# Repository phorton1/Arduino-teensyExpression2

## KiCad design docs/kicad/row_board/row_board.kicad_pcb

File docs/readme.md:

# teensyExpression2 - a Consumer End User Product

I am making this project public at this time because it is an important
step in the devlopment of the
[**vGuitar rig**](https://github.com/phorton1/phorton1/).
The documentation here is a mess!

The sotftware herein has been tested, and is working on the original
[**teensyExpression**](https://github.com/phorton1/Arduino-teensyExpression)
hardware using a new motherboard PCB that is
included in that repository.

This repository is a major revision to the *teensyExpression*, a complete
rework, that provides most of the previous functionality, and a completely
different way of **configuring the pedal**, via **preference (rig) files**
that can be transferred to and from the device via a serial interface
and the
[Buddy](https://github.com/phorton1/base-apps-buddy) and
[fileClient](https://github.com/phorton1/base-apps-fileClient) applications,
or copied to the SDCard on the teensy in an any other manner.
This new way of configuring the pedal is intended to make it
completely generalized, and usable for any purpose, without the
need to re-compile or re-install the firmware, and yet, to be, by
default, completely configured for use within the gVuitar rig.

During this re-development effort, all new Fusion 360 3D designs for the
Pedal were produced, though never printed.  During that process a serious
review of the electronics involved in the entire vGuitar rig led to a
re-thinking of its entire architecture, and the role of the teensyExpression
pedal within that architecture, leading to the notion of a new, as yet
un-created, **teensyEpression3 repository** that will contain the streamlined
and well documented source code, 3D files, kicad circuits, and so on.

I am in the *proof of concept* stage with this next step in the
vGuitar rig journey.  For anyone following along, that next step
is the new
teensyPiAudio
repository that I am initializing today as
a public repository, which will contain the work that I am doing
on a day to day basis these days.

Please feel free to peruse this repository and/or see the new
work I am doing at

**Patrick** - May 6, 2024

**p.s. - in order to do this I am pushing a large amount of uncoordinated
and unstreamlined stuff to github, particularly a bunch of new components
and footprints for **kicad**. All that will need to be cleaned up too.

## OLD

Use the looper rig as an archetype of the types of rigs that can be programmed.

Most of the other functionality of the system will be maintained, including things like

- host port?
- ftp tuning and sensitvity
- midi monitoring at excruciating levels of detail
- serial port
- debugging output to serial port or USB
- midi monitoring to serial port or USB
- midi sequences sent to serial port or USB

Before going into excruciating detail, I want to see if I can specify a
language that will let me recreate my exist looper rig.

##  Rig Basics

There will be text files on the SD card that can contain *user defined rigs*.

An *example.rig* will be provided which just happens to generate the default
**iPadLooper** rig. I will have a way to that convert that to an H file containing
the necessary parsed representation for the default constant rig.

In my const version, the default rig will have the name of **iPadLooper** and will be
used on a *factory reset*. The *default rig name* of iPadLooper will be *reserved* for
use by the system.

All **rig names** shall be limited to the characters a-z, A-z, 0-9,
space, dash, and underscore.

## Load

*Load* shall present a list of legal rig names found on the SD card
(skipping the default rig name if happens to exist on disk),
with the default rig name at the top.

A rig loaded from disk will be checked for syntactical and
functional correctness.  A failure to Load the rig will not
change anything in the system (the current rig will remain
active).

Loading a rig will place it in memory and activate it.

It is not clear at this time if the current_rig name is
stored immediately in preferences, or if it will sommehow
be tied to the preferences system.

I suspect it will be stored immediately upon a load,
and not have anything to do with the Preferences.

## Boot

Upon booting the default rig will be set into memory.
If the current_rig preference is not the same as the
default rig name, an attempt will be made to load the
given rig from the SD card.

If the named rig is succesfully loaded, it will be placed
in memory and activated.   Otherwise, default rig will
be used.

The preference will not be changed as a result of a
failure to read a file that was previously successfully
saved, although an error message WILL be generated.

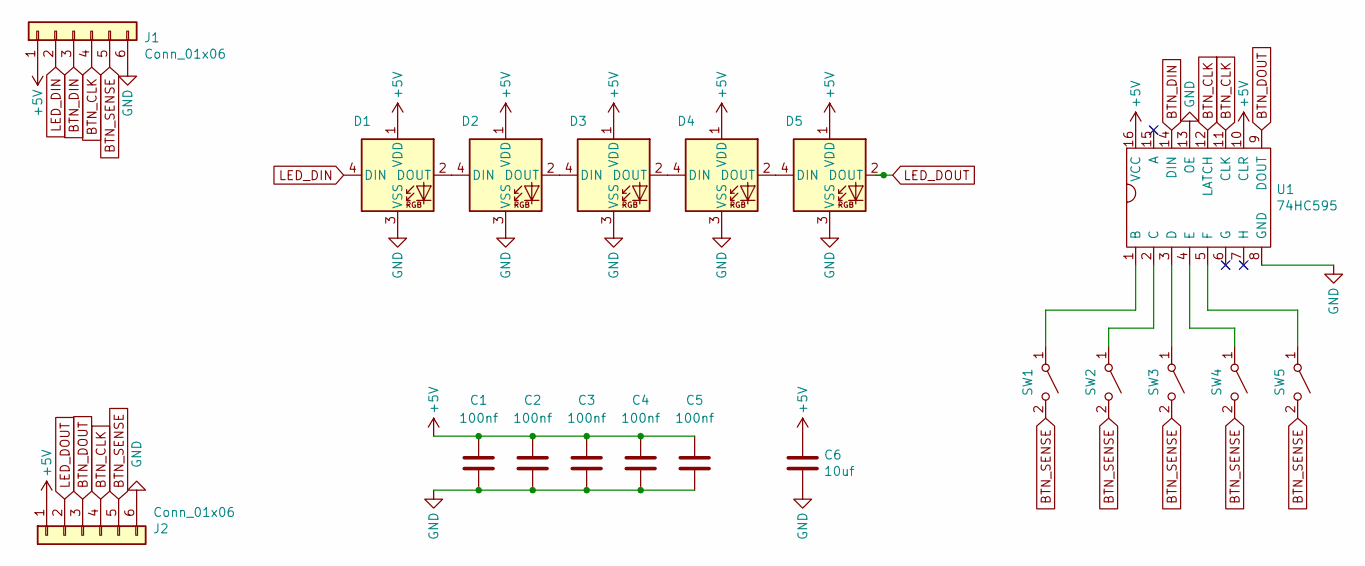
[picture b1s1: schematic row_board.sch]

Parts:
C1, C2, C3, C4, C5: 100nf; C_1206_3216Metric_Pad1.42x1.75mm_HandSolder
C6: 10uf; C_1206_3216Metric_Pad1.42x1.75mm_HandSolder
D1, D2, D3, D4, D5: WS2812B; myWS2812
J1, J2: Conn_01x06; my6Pin-08mm
SW1, SW2, SW3, SW4, SW5: SW1; mySwitchSoft
U1: 74HC595; TSSOP-16_4.4x5mm_P0.65mm

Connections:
+5V: C1.1, C2.1, C3.1, C4.1, C5.1, C6.1, D1.1 (VDD), D2.1 (VDD), D3.1 (VDD), D4.1 (VDD), D5.1 (VDD), J1.1, J2.1, U1.10 (CLR), U1.16 (VCC)
CLK: J1.4, J2.4, U1.11 (CLK), U1.12 (LATCH)
DIN: D1.4 (DIN), J1.2
DOUT: D5.2 (DOUT), J2.2
GND: C1.2, C2.2, C3.2, C4.2, C5.2, C6.2, D1.3 (VSS), D2.3 (VSS), D3.3 (VSS), D4.3 (VSS), D5.3 (VSS), J1.6, J2.6, U1.8 (GND), U1.13 (OE)
unnamed: D1.2 (DOUT), D2.4 (DIN)
unnamed: D2.2 (DOUT), D3.4 (DIN)
unnamed: D3.2 (DOUT), D4.4 (DIN)
unnamed: D4.2 (DOUT), D5.4 (DIN)
unnamed: SW1.1 (A), U1.1 (B)
unnamed: SW2.1 (A), U1.2 (C)
unnamed: SW3.1 (A), U1.3 (D)
unnamed: SW4.1 (A), U1.4 (E)
unnamed: SW5.1 (A), U1.5 (F)
SW: J1.5, J2.5, SW1.2 (B), SW2.2 (B), SW3.2 (B), SW4.2 (B), SW5.2 (B)
SWIN: J1.3, U1.14 (DIN)
SWOUT: J2.3, U1.9 (DOUT)

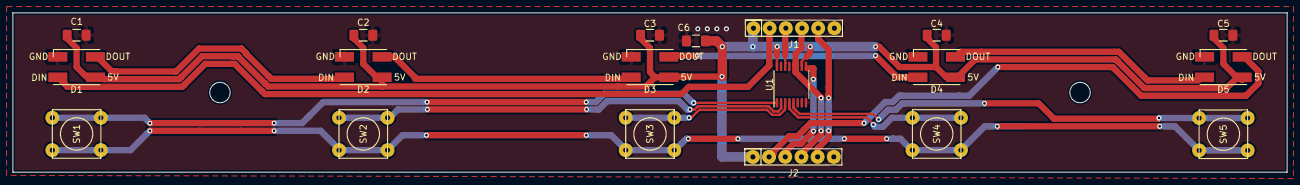
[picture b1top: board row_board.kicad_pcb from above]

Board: 2 copper layers, 200.0 x 25.0 mm, 19 parts (0 on the bottom side), 17 nets.

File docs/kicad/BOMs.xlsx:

|  |  |  | bqty | boards
 | row board | U | 74HC595 | 1 | 9
 | row board | L | WS2812b | 5 | 9
 | row board | C | 100nf | 5 | 9
 | row board | CP | 10uf | 1 | 9
 | octo interface | CP | 10uf | 6 | 3
 | octo interface | C | 2.7nf | 2 | 3
 | octo interface | C | 1.5nf | 2 | 3
 | octo interface | R | 10K | 10 | 3
 | octo interface | R | 100K | 2 | 3
 | octo interface | R | 562 | 2 | 3
 | octo interface | R | 150 | 2 | 3

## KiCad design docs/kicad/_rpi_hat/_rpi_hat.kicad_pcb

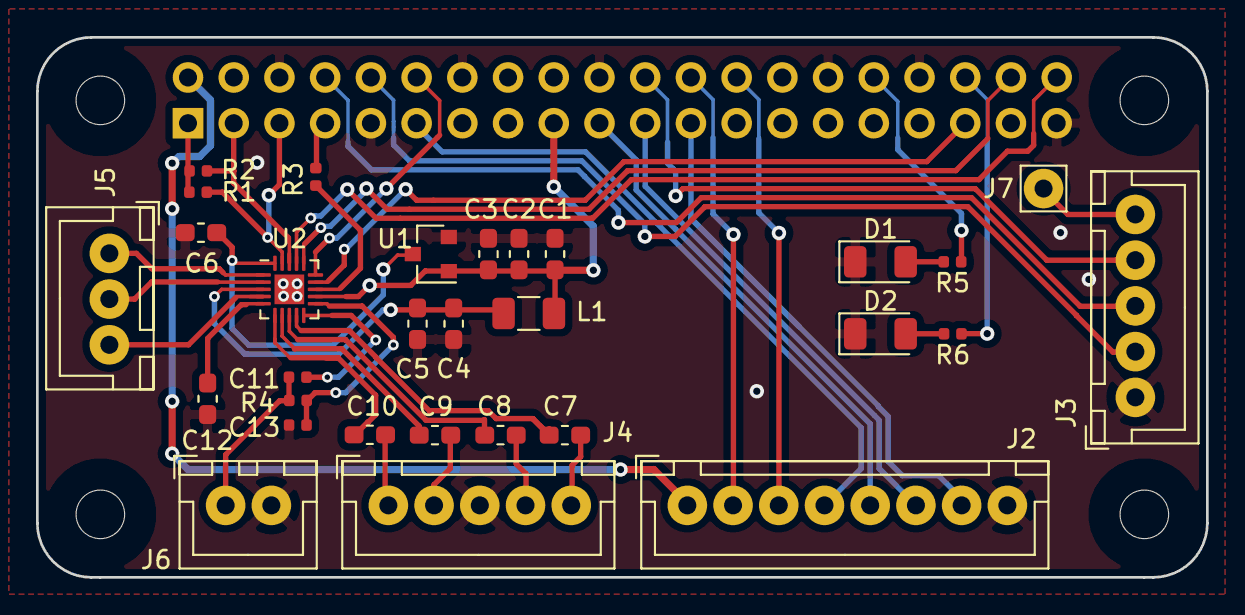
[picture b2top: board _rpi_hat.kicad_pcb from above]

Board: 2 copper layers, 65.0 x 30.0 mm, 35 parts (1 on the bottom side), 42 nets.

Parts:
C1, C4, C6, C7, C8, C9, C10: 2.2uf; C_0603_1608Metric_Pad1.05x0.95mm_HandSolder
C2, C3, C5: 0.1uf; C_0603_1608Metric_Pad1.05x0.95mm_HandSolder
C11: 0.1uf; C_0402_1005Metric
C12: 0.15uf; C_0603_1608Metric_Pad1.05x0.95mm_HandSolder
C13: 2.2uf; C_0402_1005Metric
D1, D2: LED; LED_1206_3216Metric
H1, H2, H3, H4: MountingHole; MountingHole_2.7mm_M2.5_uHAT_RPi
J1: GPIO_CONNECTOR; PinSocket_2x20_P2.54mm_Vertical_Centered_Anchor
J2: display; myJSTx08
J3: esp32; myJSTx05
J4: audio; myJSTx05
J5: HP; myJSTx03
J6: mic; myJSTx02
J7: RPI_RUN; myPinHeader_1x01
L1: Ferrite 600; L_1206_3216Metric
R1, R2, R4, R5, R6: 2.2k; R_0402_1005Metric
R3: 100; R_0402_1005Metric
U1: AP7313-18; SOT-23
U2: pauls_sgtl_5000_20; QFN-20-1EP_3x3mm_P0.4mm_EP1.65x1.65mm

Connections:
+3V3: C1.1, C2.1, C3.1, J1.1, J1.17, L1.1, R1.1, R2.1, U1.1, U2.12
+5V: J1.2, J1.4, J2.1
GND: C1.2, C2.2, C3.2, C4.2, C5.2, C6.2, C12.2, C13.2, D1.1, D2.1, J1.6, J1.9, J1.14, J1.20, J1.25, J1.30, J1.34, J1.39, J2.8, J3.1, J4.3, J6.2, U1.2, U2.21
HP_GND: J5.2, U2.2
HP_L: J5.3, U2.4
HP_R: J5.1, U2.1
I2S_RX_ACTIVE: J1.32, R5.1
I2S_TX_ACTIVE: J1.36, R6.1
LED_CS: J1.24, J2.2
LINEIN_L: C7.2, J4.5
LINEIN_R: C8.2, J4.4
LINEOUT_L: C9.2, J4.2
LINEOUT_R: C10.2, J4.1
MIC_IN: C11.2, J6.1, R4.2
MISO: J1.21, J2.6
MOSI: J1.19, J2.5
unnamed: C4.1, C5.1, L1.2, U2.3
unnamed: C6.1, U1.3, U2.20
unnamed: C7.1, U2.9
unnamed: C8.1, U2.8
unnamed: C9.1, U2.7
unnamed: C10.1, U2.6
unnamed: C11.1, U2.10
unnamed: C12.1, U2.5
unnamed: C13.1, R4.1, U2.11
unnamed: D1.2, R5.2
unnamed: D2.2, R6.2
unnamed: R3.2, U2.13
RPI_READY: J1.22, J3.4
RPI_RUN: J3.5, J7.1
RPI_RX: J1.10, J3.2
RPI_TX: J1.8, J3.3
SCL: J1.5, R1.2, U2.19
SCLK: J1.23, J2.7
SDA: J1.3, R2.2, U2.18
SGTL_BLCK: J1.12, U2.15
SGTL_FCLK: J1.35, U2.14
SGTL_I2S_IN: J1.40, U2.17
SGTL_I2S_OUT: J1.38, U2.16
SGTL_MCLK: J1.7, R3.1
TFT_CD: J1.11, J2.4
TOUCH_CS: J1.26, J2.3

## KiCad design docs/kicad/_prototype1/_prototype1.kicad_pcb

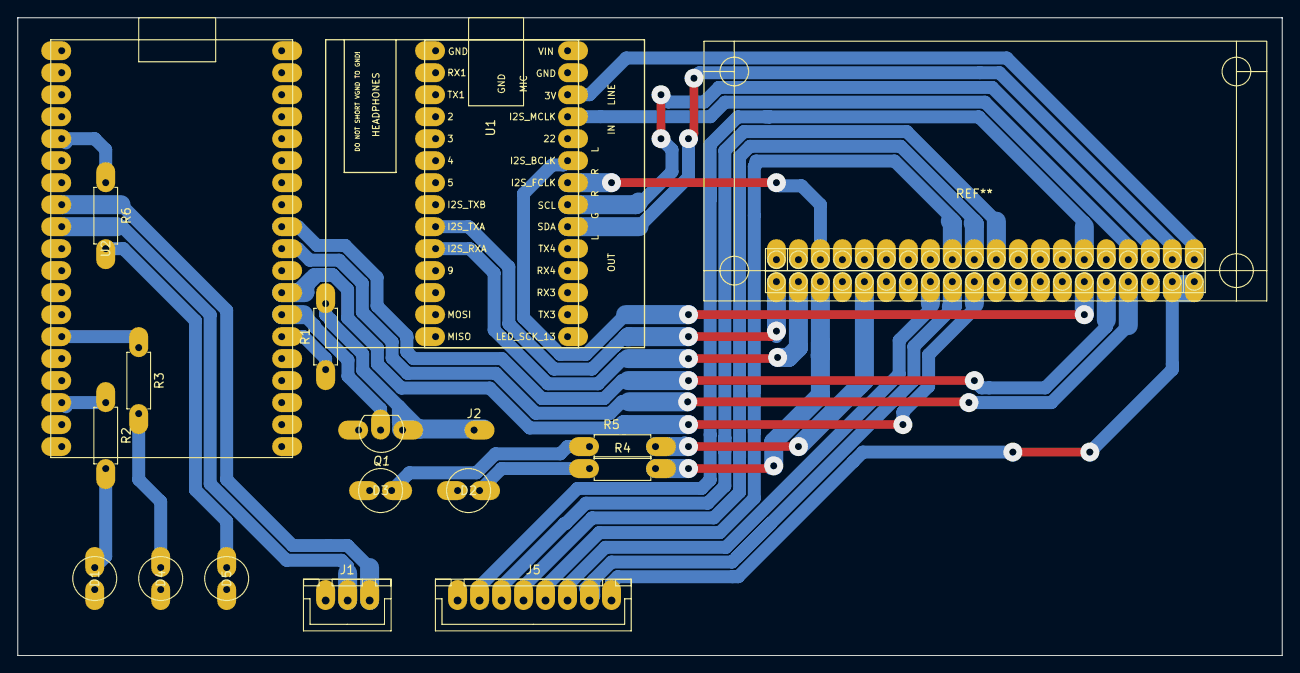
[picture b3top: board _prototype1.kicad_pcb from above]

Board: 2 copper layers, 146.1 x 73.7 mm, 19 parts (0 on the bottom side), 34 nets.

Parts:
D1: RED; led_red
D2, D3: yellow; led_yellow
D4: GREEN; led_green
D5: BLUE; led_blue
J1: T4 Serial; JST3
J2: RPI_RUN; Oval1Pin
J3: rpiB; pinSocket1x20
J4: rpiA; pinSocket1x20
J5: RPI_ILI9488; JST8
Q1: BC547; transistor
R1, R2, R3, R4, R5: 220; resistor
R6: 560; resistor
U1: teensyAudioRevD; audioShieldRevD
U2: ESP32_DEV; esp32_dev

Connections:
GND: D1.1, D2.1, D3.1, D4.1, D5.1, J1.1, J3.1, J3.8, J3.16, J4.3, J4.7, J4.10, J4.15, J4.17, J5.1, Q1.3, U1.27, U2.6, U2.20, U2.26
I2S_BCLK: J4.6, U1.23
I2S_FCLK: J3.3, U1.22
I2S_MCLK: J3.17, U1.25
I2S_RX: J4.19, U1.10
I2S_TX: J4.20, U1.9
LED_ALIVE: R2.1, U2.22
LED_PI_READY: R6.1, U2.34
LED_PI_RUN: R3.1, U2.25
unnamed: D1.2, R2.2
unnamed: D2.2, R4.1
unnamed: D3.2, R5.1
unnamed: D4.2, R3.2
unnamed: D5.2, R6.2
PI_REBOOT: Q1.2, U2.13
RPI_3V: J3.20, U1.26
RPI_5V: J4.1, J4.2, J5.8
RPI_CD: J3.15, J5.2
RPI_I2S_RX_ACTIVE: J4.16, R5.2
RPI_I2S_TX_ACTIVE: J4.18, R4.2
RPI_LED_CS: J4.12, J5.7
RPI_MISO: J3.10, J5.4
RPI_MOSI: J3.11, J5.3
RPI_READY: J4.11, U2.12
RPI_RUN: J2.1, Q1.1, R1.2
RPI_RX: J4.5, U2.9
RPI_SCL: J3.18, U1.21
RPI_SCLK: J3.9, J5.5
RPI_SDA: J3.19, U1.20
RPI_TOUCH_CS: J4.13, J5.6
RPI_TX: J4.4, U2.10
SENS_PI_RUN: R1.1, U2.14
T4_RX1: J1.2, U2.30
T4_TX1: J1.3, U2.31

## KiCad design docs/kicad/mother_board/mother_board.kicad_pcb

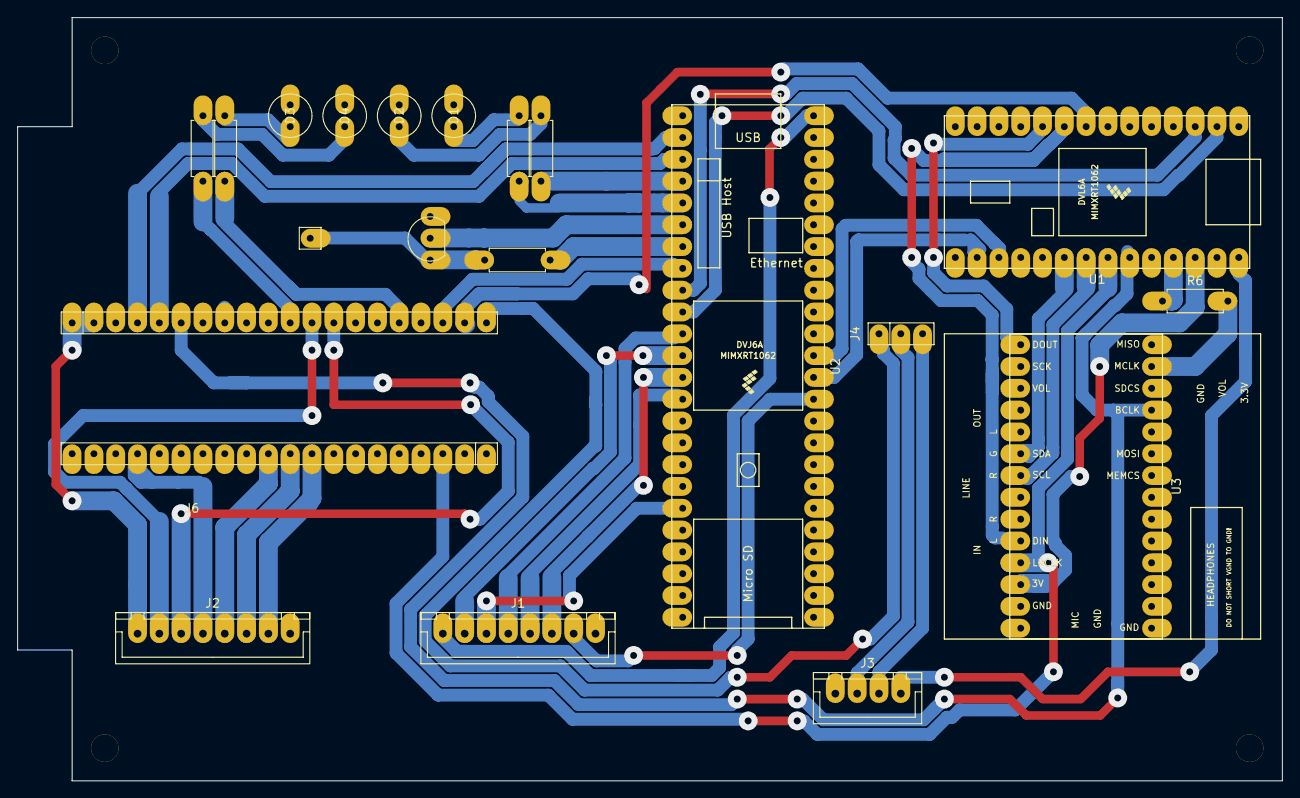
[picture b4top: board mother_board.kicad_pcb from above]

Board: 2 copper layers, 147.3 x 88.9 mm, 21 parts (0 on the bottom side), 47 nets.

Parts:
D1: GREEN; led_green
D2: BLUE; led_blue
D3, D4: YELLOW; led_yellow
J1: T3_ILI9488; JST8
J2: RPI_ILI9488; JST8
J3: USB Host; JST4
J4: 40 bottom; pinSocket1x3
J5: RPI_RUN; pinSocket1x1
J6: rpiB; pinSocket1x20
J7: rpiA; pinSocket1x20
Q1: BC547; transistor
R1, R3, R4, R5: 220; resistor
R2: 560; resistor
R6: 100; resistor
U1: myTeensy4.0; teensy40
U2: myTeensy4.1; teensy41
U3: teensyAudioRevB; audioShieldRevB

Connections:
GND: D1.1, D2.1, D3.1, D4.1, J1.8, J2.8, J3.1, J6.1, J6.8, J6.16, J7.3, J7.7, J7.10, J7.15, J7.17, Q1.3, U1.1, U1.27, U2.1, U2.34, U2.47, U3.1, U3.27
HOST_D+: J3.2, J4.2
HOST_D-: J3.3, J4.3
I2S_BCLK: J7.6, U1.23, U3.11
I2S_FCLK: J6.3, U1.22, U3.25
I2S_MCLK: R6.1, U1.25
I2S_RXA: U1.10, U3.15
I2S_RXB: J4.1, J7.20
I2S_TXA: U1.9, U3.24
I2S_TXB: J7.19, U1.8
LED_PI_READY: R2.1, U2.4
LED_PI_RUN: R1.1, U2.5
unnamed: D1.2, R1.2
unnamed: D2.2, R2.2
unnamed: D3.2, R3.2
unnamed: D4.2, R4.2
unnamed: R6.2, U3.13
PI_REBOOT: Q1.2, U2.6
RPI_5V: J2.1, J7.1, J7.2
RPI_CD: J2.4, J6.17
RPI_I2S_RX_ACTIVE: J7.11, R4.1
RPI_I2S_TX_ACTIVE: J7.16, R3.1
RPI_LED_CS: J2.2, J7.12
RPI_MISO: J2.6, J6.10
RPI_MOSI: J2.5, J6.11
RPI_READY: J7.18, U2.8
RPI_RUN: J5.1, Q1.1, R5.2
RPI_RX: J7.5, U2.3
RPI_SCLK: J2.7, J6.9
RPI_TOUCH_CS: J2.3, J7.13
RPI_TX: J7.4, U2.2
SENS_PI_RUN: R5.1, U2.7
T40_3.3V: U1.26, U3.26
T40_5V: J3.4, U1.28
T40_RX1: U1.2, U2.10
T40_RX3: U1.17, U2.37
T40_SCA: U1.20, U3.20
T40_SCL: U1.21, U3.21
T40_TX1: U1.3, U2.9
T40_TX3: U1.16, U2.36
T41_5V: J1.1, U2.48
T41_CD: J1.4, U2.11
T41_LED_CS: J1.2, U2.12
T41_MISO: J1.5, U2.14
T41_MOSI: J1.6, U2.13
T41_SCLK: J1.7, U2.35
T41_TOUCH_CS: J1.3, U2.19

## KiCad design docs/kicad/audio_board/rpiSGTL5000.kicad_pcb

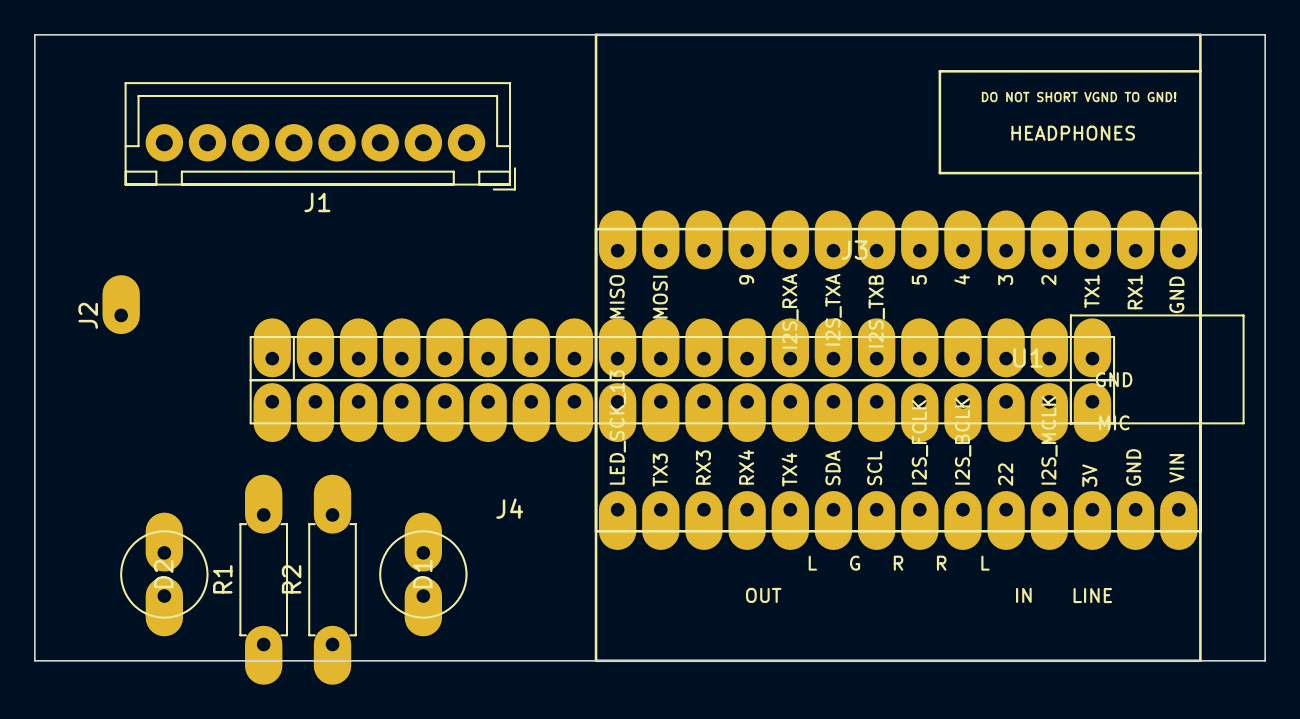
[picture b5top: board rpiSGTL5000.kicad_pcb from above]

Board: 2 copper layers, 72.4 x 36.8 mm, 9 parts (0 on the bottom side), 20 nets, no tracks yet.

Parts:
D1, D2: yellow; led_yellow
J1: display; myJSTx08
J2: RPI_RUN; Oval1Pin
J3: rpiB; pinSocket1x20_bottom
J4: rpiA; pinSocket1x20_bottom
R1, R2: 220; resistor
U1: teensyAudioRevD; audioShieldRevD

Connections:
+3V3: J3.20, U1.26
+5V: J1.8, J4.1, J4.2
GND: D1.1, D2.1, J1.1, J3.1, J3.8, J3.16, J4.3, J4.7, J4.10, J4.15, J4.17, U1.27
I2S_BCLK: J4.6, U1.23
I2S_FCLK: J3.3, U1.22
I2S_MCLK: J3.17, U1.25
I2S_RX: J4.19, U1.9
I2S_TX: J4.20, U1.10
unnamed: D1.2, R1.1
unnamed: D2.2, R2.1
RPI_CD: J1.5, J3.15
RPI_I2S_RX_ACTIVE: J4.11, R2.2
RPI_I2S_TX_ACTIVE: J4.16, R1.2
RPI_LED_CS: J1.7, J4.12
RPI_MISO: J1.3, J3.10
RPI_MOSI: J1.4, J3.11
RPI_SCLK: J1.2, J3.9
RPI_TOUCH_CS: J1.6, J4.13
SCL: J3.18, U1.21
SDA: J3.19, U1.20

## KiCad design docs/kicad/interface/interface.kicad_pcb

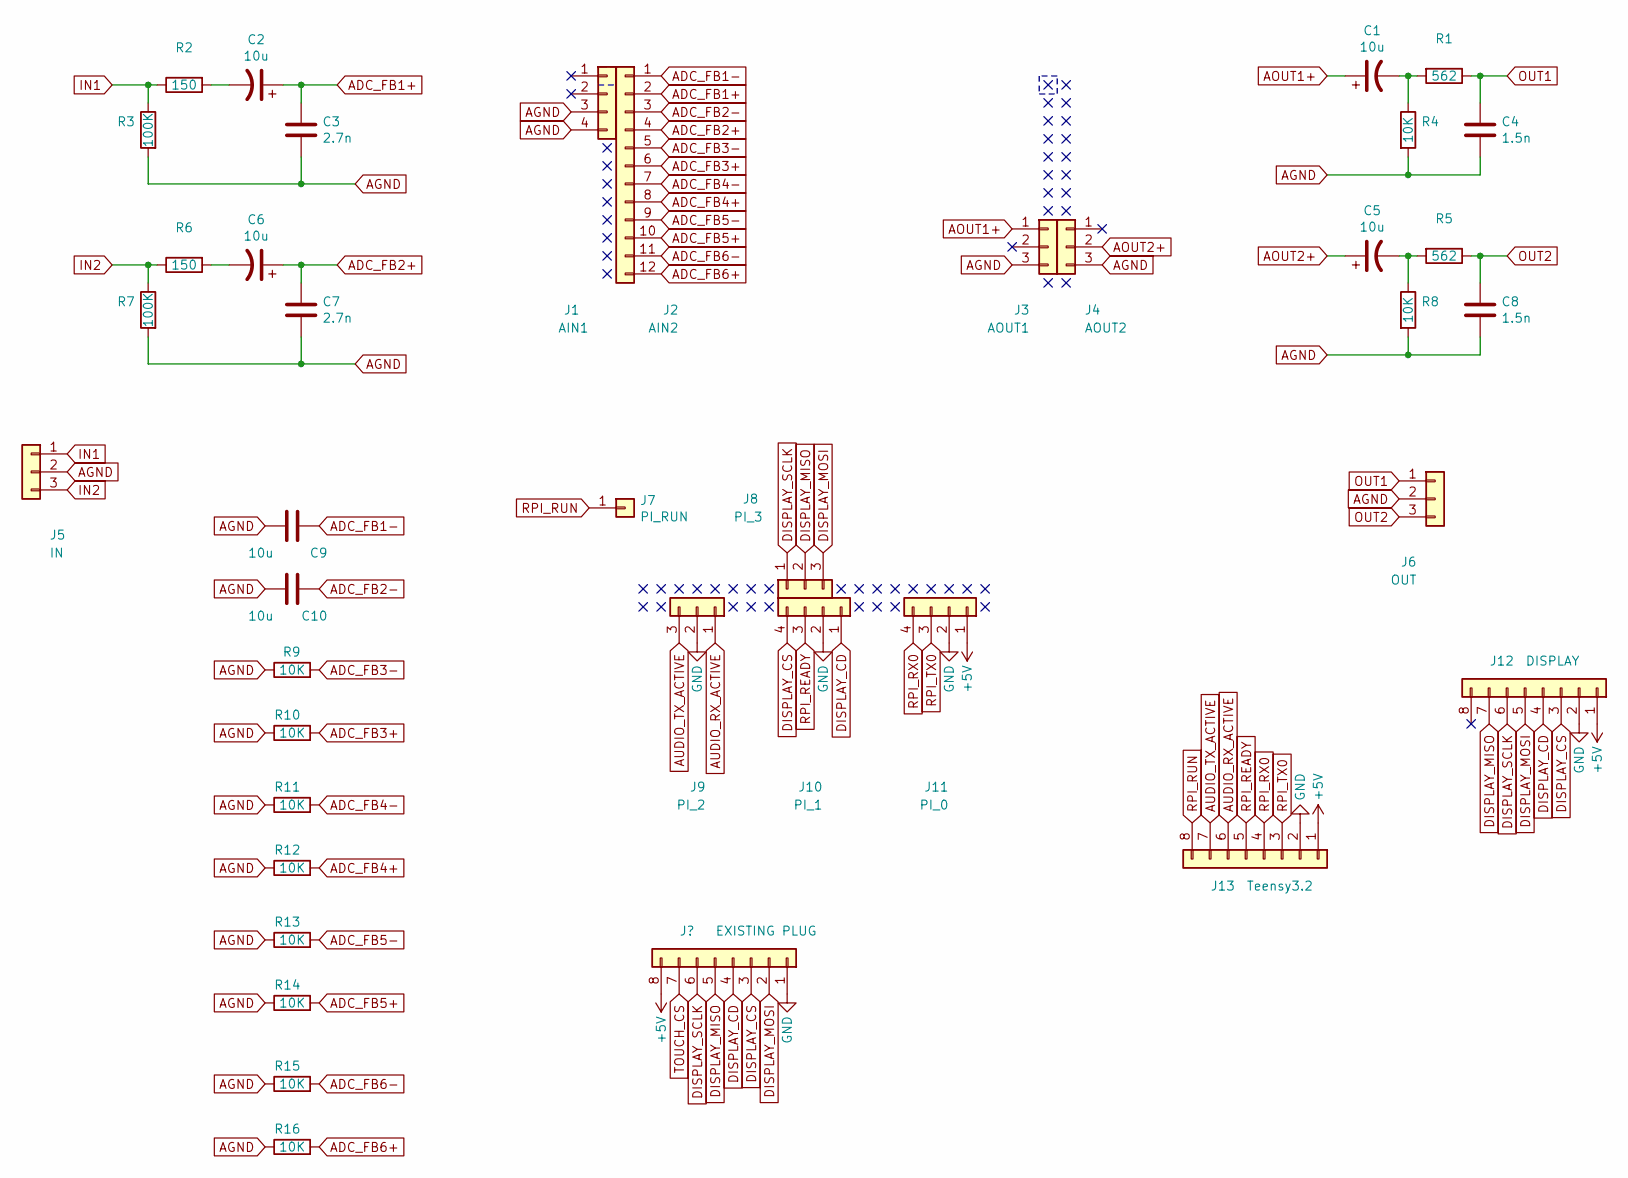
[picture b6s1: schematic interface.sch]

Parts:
C1, C2, C5, C6, C9, C10: 10u; CP_my10uf
C3, C7: 2.7n; my2pin
C4, C8: 1.5n; my2pin
J1: AIN1; my4pin
J2: AIN2; my14Pin
J3: AOUT1; my3pin
J4: AOUT2; my3pin
J5: IN; my3pin
J6: OUT; my3pin
J7: PI_RUN; my1pin
J8: PI_3; my3pin
J9: PI_2; my3pin
J10: PI_1; my4pin
J11: PI_0; my4pin
J12: DISPLAY; my8Pin
J13: Teensy3.2; my8Pin
R1, R5: 562; myResistor
R2, R6: 150; myResistor
R3, R7: 100K; myResistor
R4, R8, R9, R10, R11, R12, R13, R14, R15, R16: 10K; myResistor

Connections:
+5V: J11.1, J12.1, J13.1
ADC_FB1+: C2.1, C3.1, J2.2
ADC_FB1-: C9.1, J2.1
ADC_FB2+: C6.1, C7.1, J2.4
ADC_FB2-: C10.1, J2.3
ADC_FB3+: J2.6, R10.2
ADC_FB3-: J2.5, R9.2
ADC_FB4+: J2.8, R12.2
ADC_FB4-: J2.7, R11.2
ADC_FB5+: J2.10, R14.2
ADC_FB5-: J2.9, R13.2
ADC_FB6+: J2.12, R16.2
ADC_FB6-: J2.11, R15.2
AGND: C3.2, C4.2, C7.2, C8.2, C9.2, C10.2, J1.3, J1.4, J3.3, J4.3, J5.2, J6.2, R3.2, R4.2, R7.2, R8.2, R9.1, R10.1, R11.1, R12.1, R13.1, R14.1, R15.1, R16.1
AOUT1+: C1.1, J3.1
AOUT2+: C5.1, J4.2
AUDIO_RX_ACTIVE: J9.1, J13.6
AUDIO_TX_ACTIVE: J9.3, J13.7
DISPLAY_CD: J10.1, J12.4
DISPLAY_CS: J10.4, J12.3
DISPLAY_MISO: J8.2, J12.7
DISPLAY_MOSI: J8.3, J12.5
DISPLAY_SCLK: J8.1, J12.6
IN1: J5.1, R2.1, R3.1
IN2: J5.3, R6.1, R7.1
unnamed: C1.2, R1.2, R4.1
unnamed: C2.2, R2.2
unnamed: C5.2, R5.2, R8.1
unnamed: C6.2, R6.2
OUT1: C4.1, J6.1, R1.1
OUT2: C8.1, J6.3, R5.1
RPI_READY: J10.3, J13.5
RPI_RUN: J7.1, J13.8
RPI_RX0: J11.4, J13.4
RPI_TX0: J11.3, J13.3

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
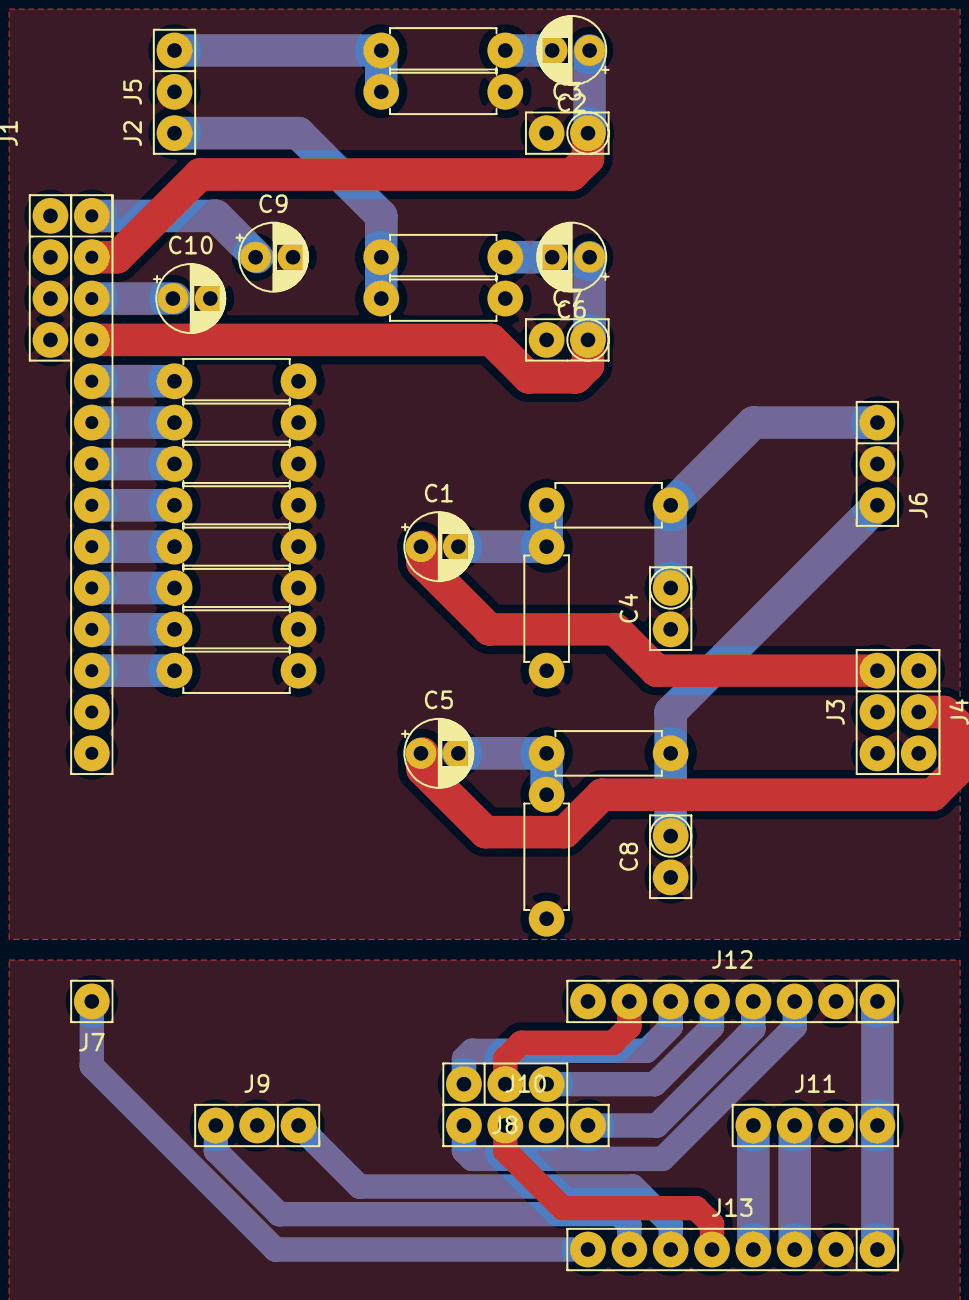
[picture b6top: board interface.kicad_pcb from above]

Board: 2 copper layers, 39 parts (0 on the bottom side), 36 nets.

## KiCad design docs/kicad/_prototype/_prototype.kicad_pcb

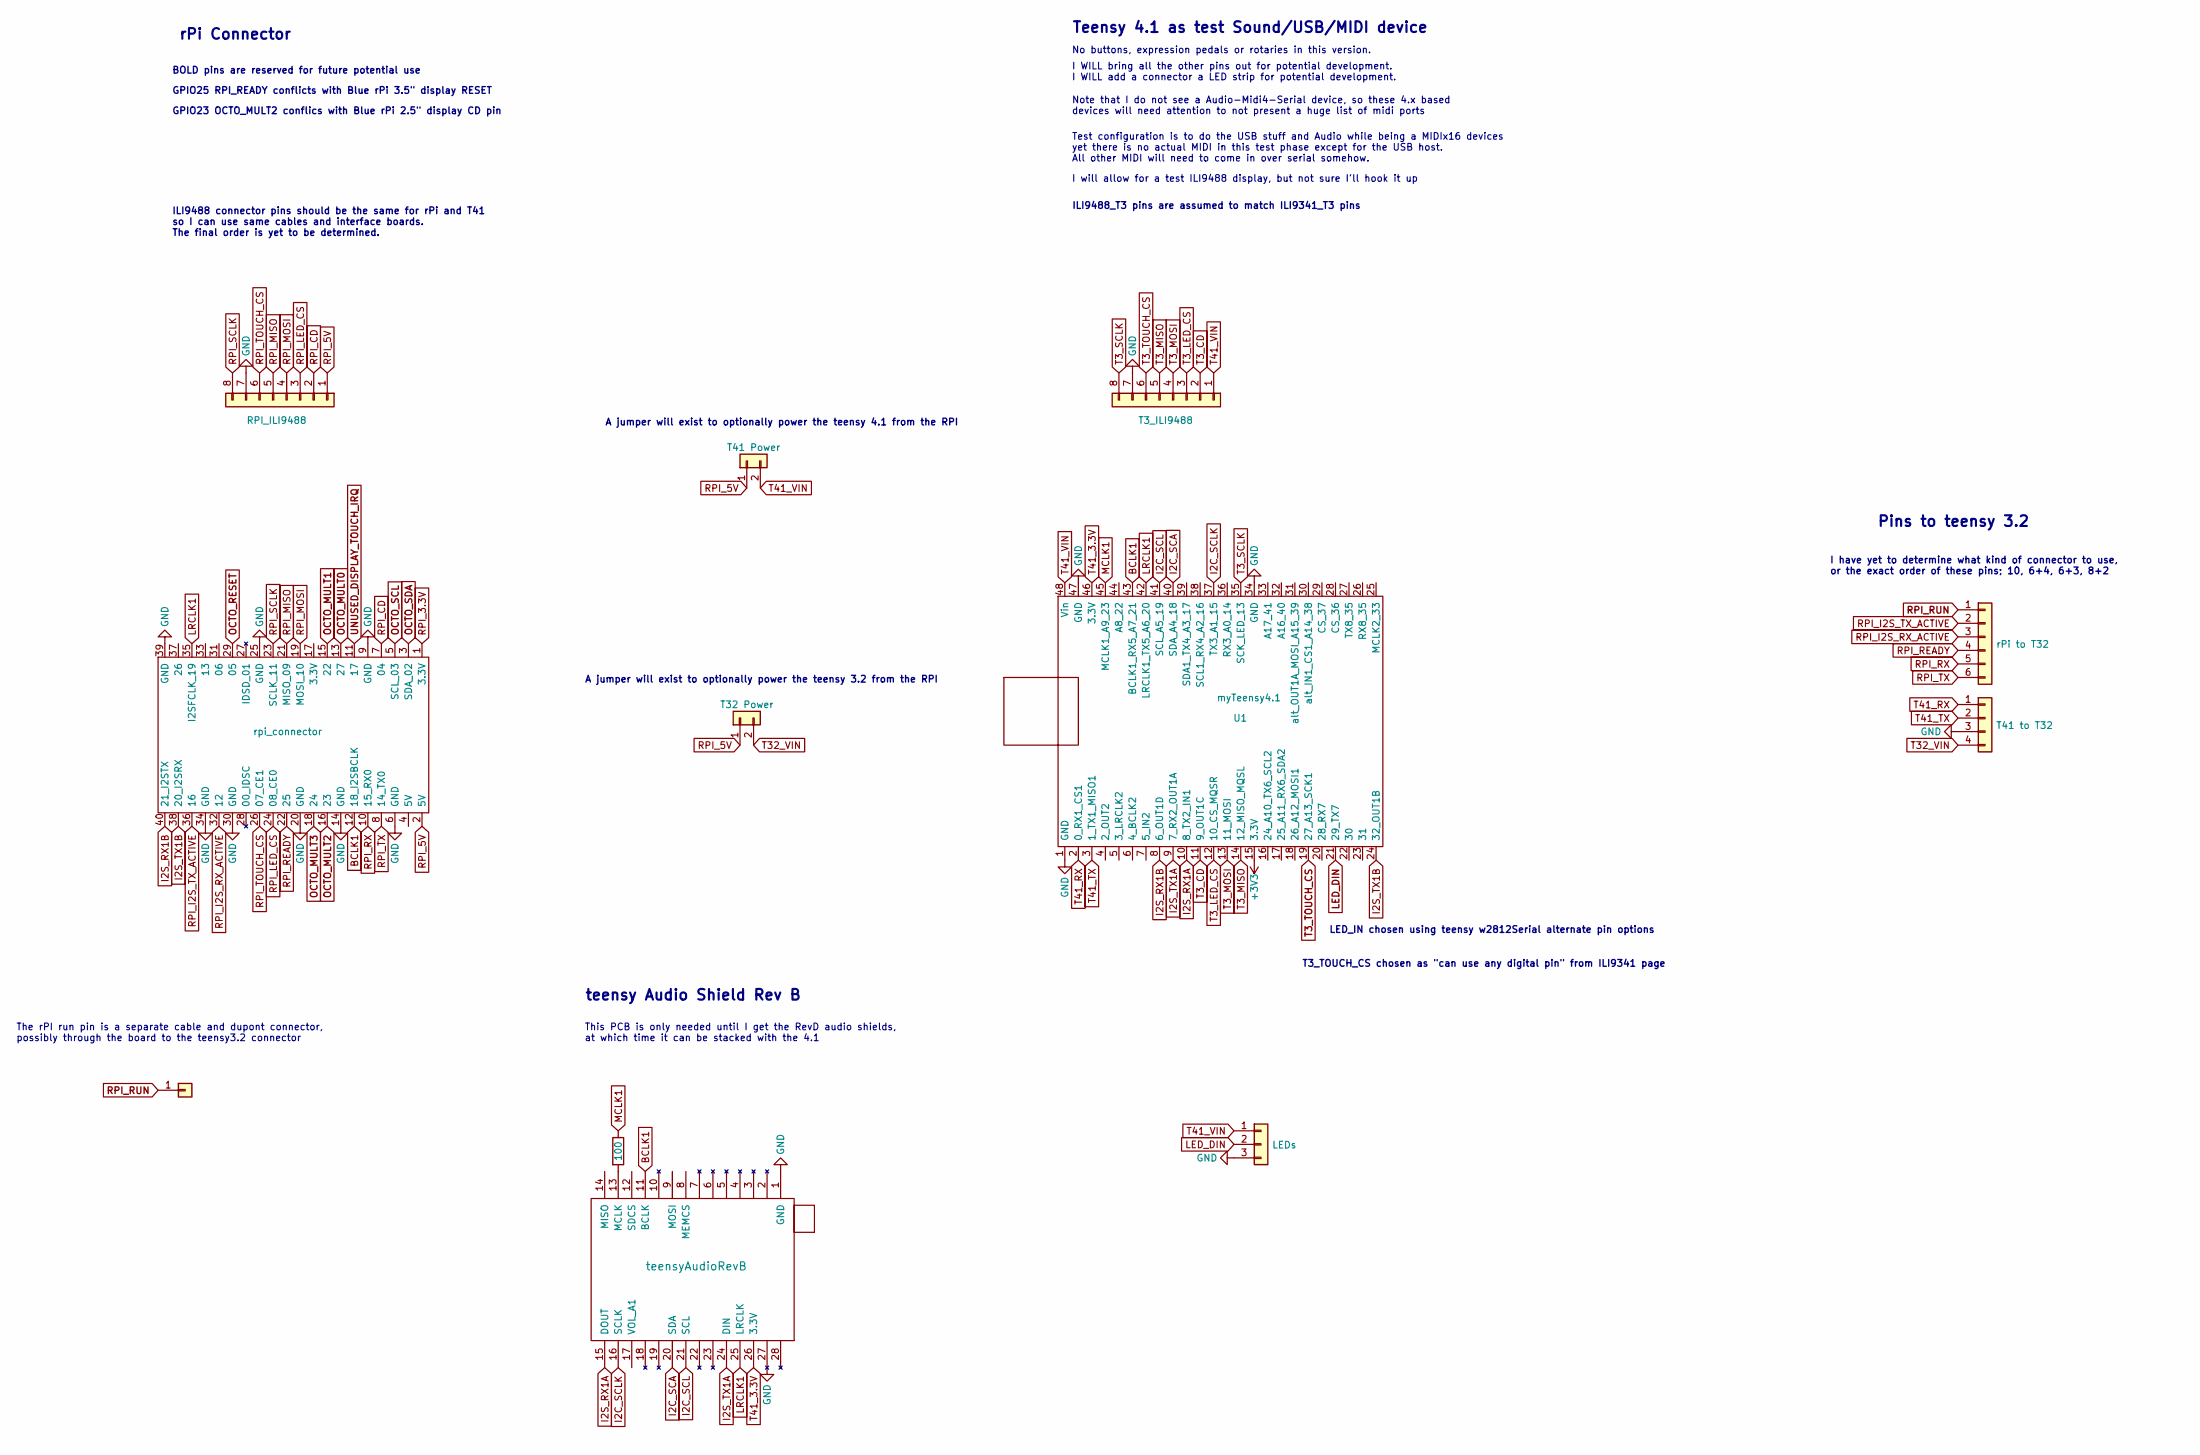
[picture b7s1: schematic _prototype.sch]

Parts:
J1: T3_ILI9488; myJSTx08
J2: RPI_ILI9488; myJSTx08
J3: T41 Power; myPinHeader_1x02
J5: rPi to T32; myJSTx06
J6: T32 Power; myPinHeader_1x02
J7: T41 to T32; myJSTx04
J8: rpi_connector; myRpiConnector
J9: RPI_RUN; my1pin
J10: LEDs; myJSTx03
R1: 100; myResistor
U1: myTeensy4.1; myTeensy41
U2: teensyAudioRevB; audioShieldRevB

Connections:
+3V3: U1.15 (3.3V)
BCLK1: J8.12 (18_I2SBCLK), U1.43 (BCLK1_RX5_A7_21), U2.11 (BCLK)
GND: J1.7, J2.7, J7.3, J8.6 (GND), J8.9 (GND), J8.14 (GND), J8.20 (GND), J8.25 (GND), J8.30 (GND), J8.34 (GND), J8.39 (GND), J10.3, U1.1 (GND), U1.34 (GND), U1.47 (GND), U2.1 (GND), U2.27
I2C_SCA: U1.40 (SDA_A4_18), U2.20 (SDA)
I2C_SCL: U1.41 (SCL_A5_19), U2.21 (SCL)
I2C_SCLK: U1.37 (TX3_A1_15), U2.16 (SCLK)
I2S_RX1A: U1.10 (8_TX2_IN1), U2.15 (DOUT)
I2S_RX1B: J8.40 (21_I2STX), U1.8 (6_OUT1D)
I2S_TX1A: U1.9 (7_RX2_OUT1A), U2.24 (DIN)
I2S_TX1B: J8.38 (20_I2SRX), U1.24 (32_OUT1B)
LED_DIN: J10.2, U1.21 (29_TX7)
LRCLK1: J8.35 (I2SFCLK_19), U1.42 (LRCLK1_TX5_A6_20), U2.25 (LRCLK)
MCLK1: R1.1, U1.45 (MCLK1_A9_23)
unnamed: R1.2, U2.13 (MCLK)
OCTO_MULT0: J8.13 (27)
OCTO_MULT1: J8.15 (22)
OCTO_MULT2: J8.16 (23)
OCTO_MULT3: J8.18 (24)
OCTO_RESET: J8.29 (05)
OCTO_SCL: J8.5 (SCL_03)
OCTO_SDA: J8.3 (SDA_02)
RPI_3.3V: J8.1 (3.3V)
RPI_5V: J2.1, J3.1, J6.1, J8.2 (5V)
RPI_CD: J2.2, J8.7 (04)
RPI_I2S_RX_ACTIVE: J5.3, J8.32 (12)
RPI_I2S_TX_ACTIVE: J5.2, J8.36 (16)
RPI_LED_CS: J2.3, J8.24 (08_CE0)
RPI_MISO: J2.5, J8.21 (MISO_09)
RPI_MOSI: J2.4, J8.19 (MOSI_10)
RPI_READY: J5.4, J8.22 (25)
RPI_RUN: J5.1, J9.1
RPI_RX: J5.5, J8.10 (15_RX0)
RPI_SCLK: J2.8, J8.23 (SCLK_11)
RPI_TOUCH_CS: J2.6, J8.26 (07_CE1)
RPI_TX: J5.6, J8.8 (14_TX0)
T3_CD: J1.2, U1.11 (9_OUT1C)
T3_LED_CS: J1.3, U1.12 (10_CS_MQSR)
T3_MISO: J1.5, U1.14 (12_MISO_MQSL)
T3_MOSI: J1.4, U1.13 (11_MOSI)
T3_SCLK: J1.8, U1.35 (SCK_LED_13)
T3_TOUCH_CS: J1.6, U1.19 (27_A13_SCK1)
T32_VIN: J6.2, J7.4
T41_3.3V: U1.46 (3.3V), U2.26 (3.3V)
T41_RX: J7.1, U1.2 (0_RX1_CS1)
T41_TX: J7.2, U1.3 (1_TX1_MISO1)
T41_VIN: J1.1, J3.2, J10.1, U1.48 (Vin)
UNUSED_DISPLAY_TOUCH_IRQ: J8.11 (17)

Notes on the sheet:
GPIO25 RPI_READY conflicts with Blue rPi 3.5" display RESET
GPIO23 OCTO_MULT2 conflics with Blue rPi 2.5" display CD pin
LED_IN chosen using teensy w2812Serial alternate pin options
T3_TOUCH_CS chosen as "can use any digital pin" from ILI9341 page
BOLD pins are reserved for future potential use
rPi Connector
teensy Audio Shield Rev B
This PCB is only needed until I get the RevD audio shields, at which time it can be stacked with the 4.1
ILI9488_T3 pins are assumed to match ILI9341_T3 pins
Teensy 4.1 as test Sound/USB/MIDI device
Note that I do not see a Audio-Midi4-Serial device, so these 4.x based devices will need attention to not present a huge list of midi ports
Test configuration is to do the USB stuff and Audio while being a MIDIx16 devices yet there is no actual MIDI in this test phase except for the USB host. All other MIDI will need to come in over serial somehow.
I will allow for a test ILI9488 display, but not sure I'll hook it up
No buttons, expression pedals or rotaries in this version.
I WILL bring all the other pins out for potential development. I WILL add a connector a LED strip for potential development.
ILI9488 connector pins should be the same for rPi and T41 so I can use same cables and interface boards. The final order is yet to be determined.
Pins to teensy 3.2
I have yet to determine what kind of connector to use, or the exact order of these pins; 10, 6+4, 6+3, 8+2
The rPI run pin is a separate cable and dupont connector, possibly through the board to the teensy3.2 connector
A jumper will exist to optionally power the teensy 4.1 from the RPI
A jumper will exist to optionally power the teensy 3.2 from the RPI

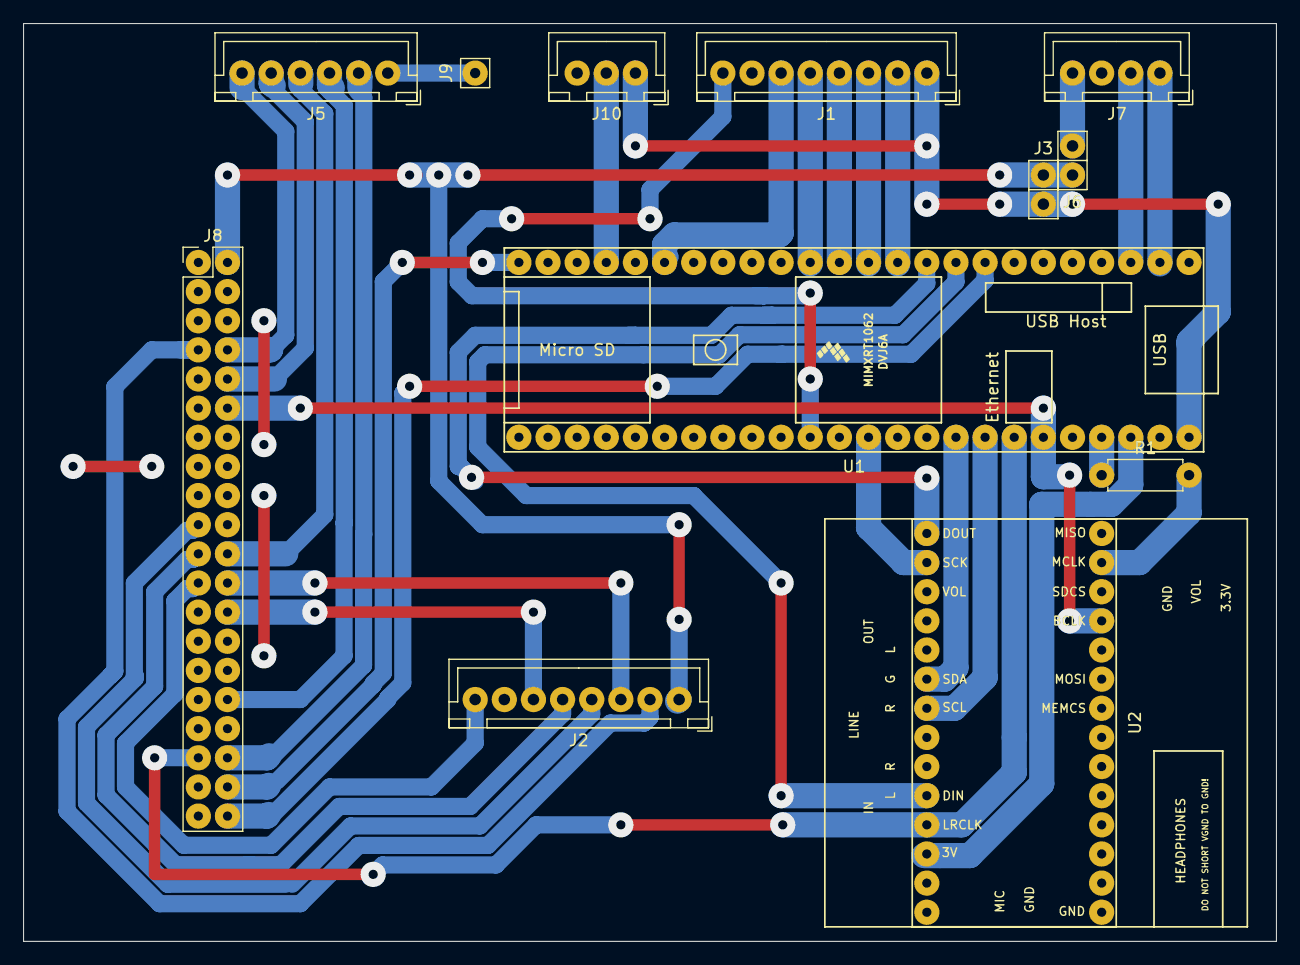
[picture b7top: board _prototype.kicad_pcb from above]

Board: 2 copper layers, 109.2 x 80.0 mm, 12 parts (0 on the bottom side), 37 nets.

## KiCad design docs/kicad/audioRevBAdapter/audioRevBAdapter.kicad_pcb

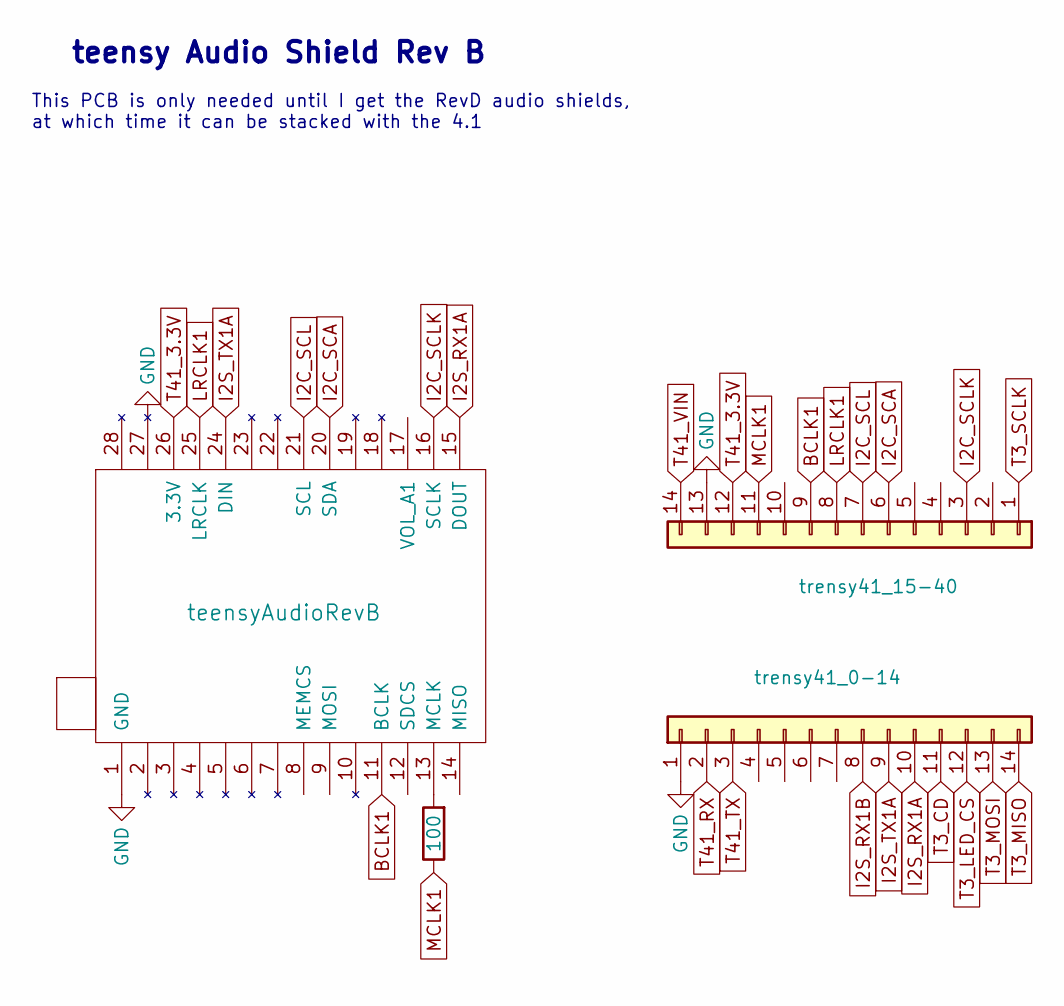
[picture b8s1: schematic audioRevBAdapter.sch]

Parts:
J1: trensy41_15-40; myPinSocket_1x14
J2: trensy41_0-14; myPinSocket_1x14
R1: 100; myResistor
U2: teensyAudioRevB; audioShieldRevB

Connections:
BCLK1: J1.9, U2.11 (BCLK)
GND: J1.13, J2.1, U2.1 (GND), U2.27
I2C_SCA: J1.6, U2.20 (SDA)
I2C_SCL: J1.7, U2.21 (SCL)
I2C_SCLK: J1.3, U2.16 (SCLK)
I2S_RX1A: J2.10, U2.15 (DOUT)
I2S_RX1B: J2.8
I2S_TX1A: J2.9, U2.24 (DIN)
LRCLK1: J1.8, U2.25 (LRCLK)
MCLK1: J1.11, R1.1
unnamed: R1.2, U2.13 (MCLK)
T3_CD: J2.11
T3_LED_CS: J2.12
T3_MISO: J2.14
T3_MOSI: J2.13
T3_SCLK: J1.1
T41_3.3V: J1.12, U2.26 (3.3V)
T41_RX: J2.2
T41_TX: J2.3
T41_VIN: J1.14

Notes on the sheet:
teensy Audio Shield Rev B
This PCB is only needed until I get the RevD audio shields, at which time it can be stacked with the 4.1

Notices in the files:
docs/kicad/_rpi_hat/_rpi_hat.kicad_pcb:
This PCB design is licensed under MIT Open Source License.
